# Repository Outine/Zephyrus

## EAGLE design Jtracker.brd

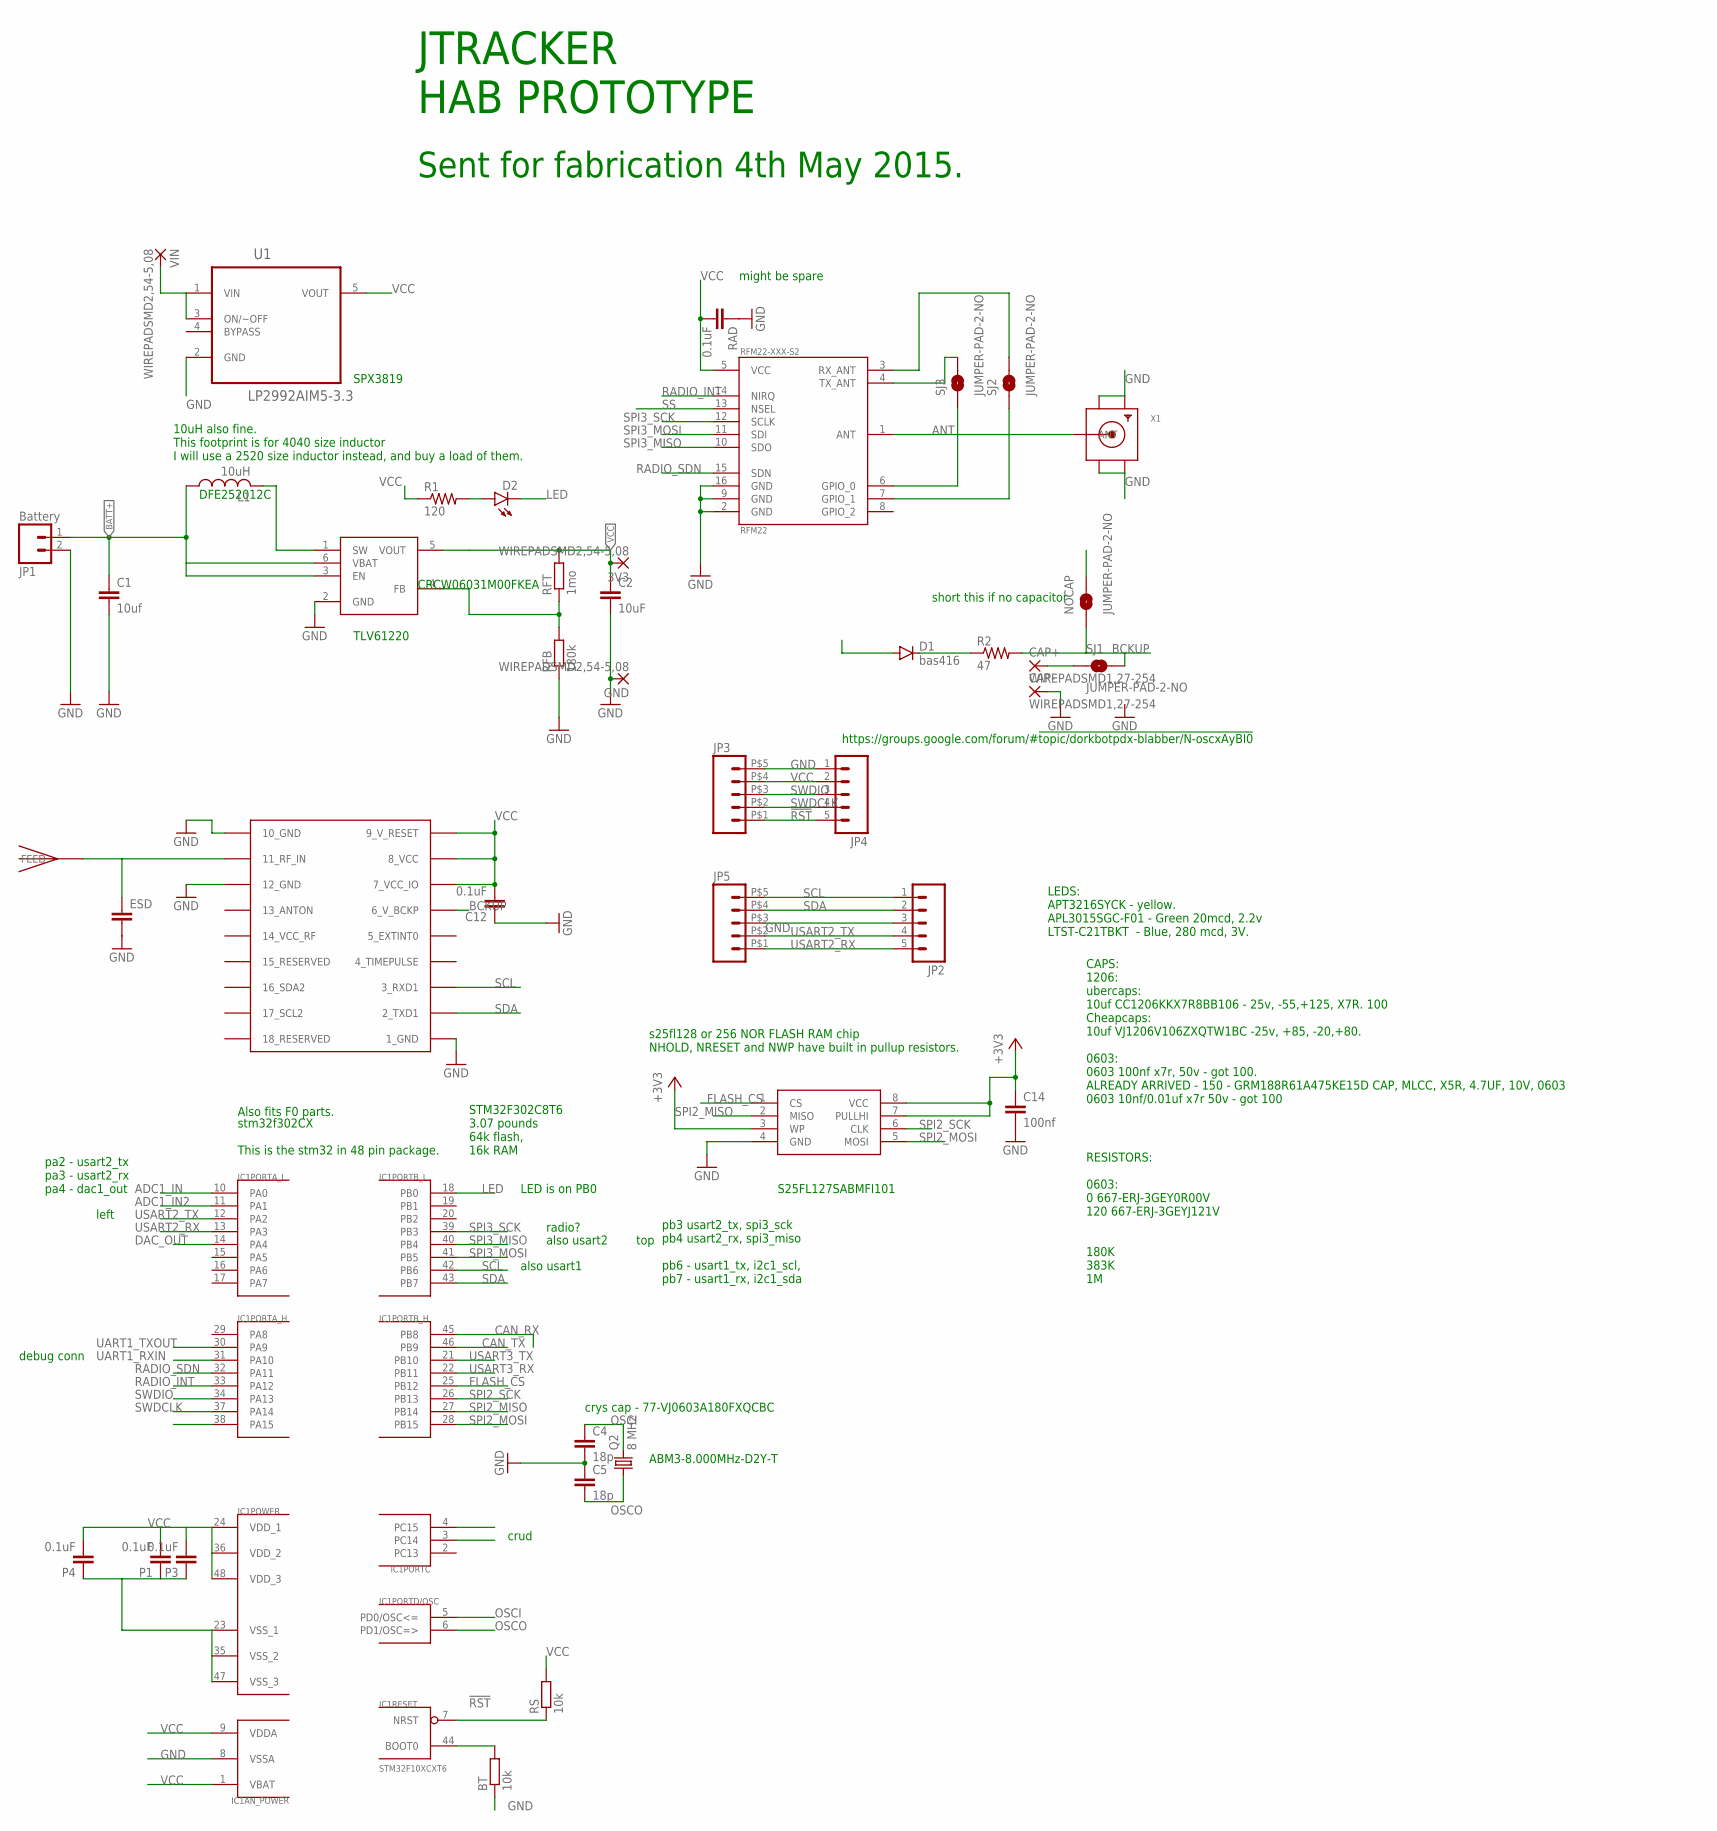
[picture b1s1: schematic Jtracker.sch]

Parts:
3V3: WIREPADSMD2,54-5,08; SMD2,54-5,08
BT: 10k; R0603
C1: 10uf; 1206
C2: 10uF; 1206
C4, C5: 18p; C0603
C12: 0.1uF; C0603
C14: 100nf; 0603-CAP
CAP+: WIREPADSMD1,27-254; SMD1,27-2,54
CAP-: WIREPADSMD1,27-254; SMD1,27-2,54
D1: bas416; SOD-123
D2: LED1206; LED-1206
ESD: CAP0603-CAP; 0603-CAP
GND: WIREPADSMD2,54-5,08; SMD2,54-5,08
GPS_ANT: JTI_ANTENNA-1575AT43A40
IC1: STM32F10XCXT6; TQFP48
JP1: Battery; 1X02
JP2, JP4: M05NO_SILK; 1X05_NO_SILK
JP3, JP5: M05; 5PADSMD
L1: 10uH; LQH44
MEM: S25FL127S_SOIC; SOIC-8W
NOCAP: JUMPER-PAD-2-NO; PAD-JUMPER-2-NO_NO_SILK
P1, P3, P4: 0.1uF; C0603
Q2: 8 MHz; ABRACON_ABM3_CRYSTAL
R1: 120; 0603-RES
R2: 47; 0603-RES
RAD: 0.1uF; C0603
RFB: 180k; R0603
RFM22-XXX-S2: RFM22; RFM22-XXX-S2
RFT: 1mo; R0603
RS: 10k; R0603
SJ1, SJ2, SJ3: JUMPER-PAD-2-NO; PAD-JUMPER-2-NO_NO_SILK
U1: LP2992AIM5-3.3; SOT95P284X122-5N
U$2: TLV61220; SOT23-6
U$3: UBLOX_MAX
VIN: WIREPADSMD2,54-5,08; SMD2,54-5,08
X1: SMACONNECTOR_EDGE_UFL; SMA_EDGELAUNCH_UFL

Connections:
!RST: IC1.7 (NRST), JP3.P$1 (1), JP4.5, RS.1
+3V3: MEM.3 (WP)
ADC1_IN: IC1.10 (PA0)
ADC1_IN2: IC1.11 (PA1)
ANT: RFM22-XXX-S2.1 (ANT), X1.P (ANT)
BATT+: C1.1, JP1.1, L1.P$1 (1), U$2.3 (EN), U$2.6 (VBAT)
BCKUP: NOCAP.1, R2.2, SJ1.2, U$3.6_V_BCKP
CAN_RX: IC1.45 (PB8)
CAN_TX: IC1.46 (PB9)
DAC_OUT: IC1.14 (PA4)
FLASH_CS: IC1.25 (PB12), MEM.1 (CS)
GND: BT.1, C1.2, C2.2, C4.2, C5.1, C12.1, C14.2, CAP-.1, ESD.2, GND.1, IC1.8 (VSSA), IC1.23 (VSS_1), IC1.35 (VSS_2), IC1.47 (VSS_3), JP1.2, JP2.3, JP3.P$5 (5), JP4.1, JP5.P$3 (3), MEM.4 (GND), P1.1, P3.1, P4.1, RAD.1, RFB.1, RFM22-XXX-S2.2 (GND), RFM22-XXX-S2.9 (GND), RFM22-XXX-S2.16 (GND), U1.2 (GND), U$2.2 (GND), U$3.1_GND, U$3.10_GND, U$3.12_GND, X1.GND@1 (GND1), X1.GND@2 (GND2), X1.GND@3 (GND3), X1.GND@4 (GND4)
GPS_ANT: ESD.1, GPS_ANT.FEED, U$3.11_RF_IN
LED: D2.C, IC1.18 (PB0)
unnamed: D1.C, R2.1
unnamed: U1.1 (VIN), U1.3 (ON/~OFF), VIN.1
unnamed: BT.2, IC1.44 (BOOT0)
unnamed: RFM22-XXX-S2.4 (TX_ANT), SJ3.2
unnamed: RFM22-XXX-S2.3 (RX_ANT), SJ2.2
unnamed: L1.P$2 (2), U$2.1 (SW)
unnamed: CAP+.1, SJ1.1
unnamed: RFM22-XXX-S2.7 (GPIO_1), SJ2.1
unnamed: RFB.2, RFT.1, U$2.4 (FB)
unnamed: RFM22-XXX-S2.6 (GPIO_0), SJ3.1
unnamed: D2.A, R1.2
OSCI: C4.1, IC1.5 (PD0/OSC<=), Q2.P$2 (2)
OSCO: C5.2, IC1.6 (PD1/OSC=>), Q2.P$1 (1)
RADIO_INT: IC1.33 (PA12), RFM22-XXX-S2.14 (NIRQ)
RADIO_SDN: IC1.32 (PA11), RFM22-XXX-S2.15 (SDN)
SCL: IC1.42 (PB6), JP2.1, JP5.P$5 (5), U$3.3_RXD1
SDA: IC1.43 (PB7), JP2.2, JP5.P$4 (4), U$3.2_TXD1
SPI2_MISO: IC1.27 (PB14), MEM.2 (MISO)
SPI2_MOSI: IC1.28 (PB15), MEM.5 (MOSI)
SPI2_SCK: IC1.26 (PB13), MEM.6 (CLK)
SPI3_MISO: IC1.40 (PB4), RFM22-XXX-S2.10 (SDO)
SPI3_MOSI: IC1.41 (PB5), RFM22-XXX-S2.11 (SDI)
SPI3_SCK: IC1.39 (PB3), RFM22-XXX-S2.12 (SCLK)
SS: IC1.38 (PA15), RFM22-XXX-S2.13 (NSEL)
SWDCLK: IC1.37 (PA14), JP3.P$2 (2), JP4.4
SWDIO: IC1.34 (PA13), JP3.P$3 (3), JP4.3
UART1_RXIN: IC1.31 (PA10)
UART1_TXOUT: IC1.30 (PA9)
USART2_RX: IC1.13 (PA3), JP2.5, JP5.P$1 (1)
USART2_TX: IC1.12 (PA2), JP2.4, JP5.P$2 (2)
USART3_RX: IC1.22 (PB11)
USART3_TX: IC1.21 (PB10)
VCC: 3V3.1, C2.1, C12.2, C14.1, D1.A, IC1.1 (VBAT), IC1.9 (VDDA), IC1.24 (VDD_1), IC1.36 (VDD_2), IC1.48 (VDD_3), JP3.P$4 (4), JP4.2, MEM.7 (PULLHI), MEM.8 (VCC), NOCAP.2, P1.2, P3.2, P4.2, R1.1, RAD.2, RFM22-XXX-S2.5 (VCC), RFT.2, RS.2, U1.5 (VOUT), U$2.5 (VOUT), U$3.7_VCC_IO, U$3.8_VCC, U$3.9_V_RESET

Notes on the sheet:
https://groups.google.com/forum/#!topic/dorkbotpdx-blabber/N-oscxAyBI0
stm32f302CX This is the stm32 in 48 pin package.
also usart1
also usart2
radio?
debug conn
crud
left
top
pb3 usart2_tx, spi3_sck pb4 usart2_rx, spi3_miso pb6 - usart1_tx, i2c1_scl, pb7 - usart1_rx, i2c1_sda
pa2 - usart2_tx pa3 - usart2_rx pa4 - dac1_out
s25fl128 or 256 NOR FLASH RAM chip NHOLD, NRESET and NWP have built in pullup resistors.
short this if no capacitor
might be spare
10uH also fine. This footprint is for 4040 size inductor I will use a 2520 size inductor instead, and buy a load of them.
JTRACKER HAB PROTOTYPE
Sent for fabrication 4th May 2015.
ABM3-8.000MHz-D2Y-T
TLV61220
crys cap - 77-VJ0603A180FXQCBC
S25FL127SABMFI101
CRCW06031M00FKEA
DFE252012C
SPX3819
STM32F302C8T6 3.07 pounds 64k flash, 16k RAM
LEDS: APT3216SYCK - yellow. APL3015SGC-F01 - Green 20mcd, 2.2v LTST-C21TBKT - Blue, 280 mcd, 3V.
CAPS: 1206: ubercaps: 10uf CC1206KKX7R8BB106 - 25v, -55,+125, X7R. 100 Cheapcaps: 10uf VJ1206V106ZXQTW1BC -25v, +85, -20,+80. 0603: 0603 100nf x7r, 50v - got 100. ALREADY ARRIVED - 150 - GRM188R61A475KE15D CAP, MLCC, X5R, 4.7UF, 10V, 0603 0603 10nf/0.01uf x7r 50v - got 100
RESISTORS: 0603: 0 667-ERJ-3GEY0R00V 120 667-ERJ-3GEYJ121V 180K 383K 1M
Also fits F0 parts.
LED is on PB0

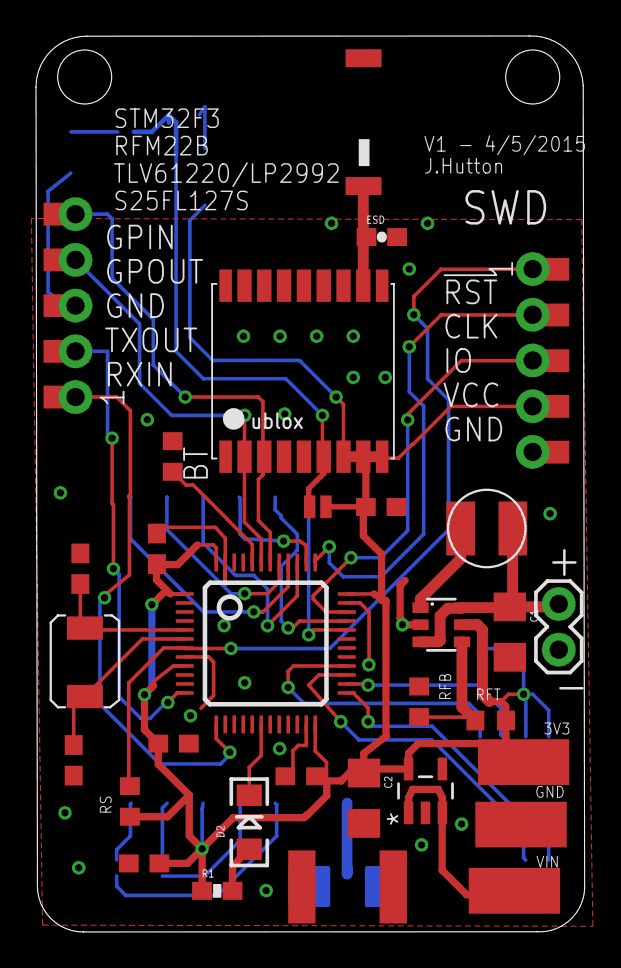
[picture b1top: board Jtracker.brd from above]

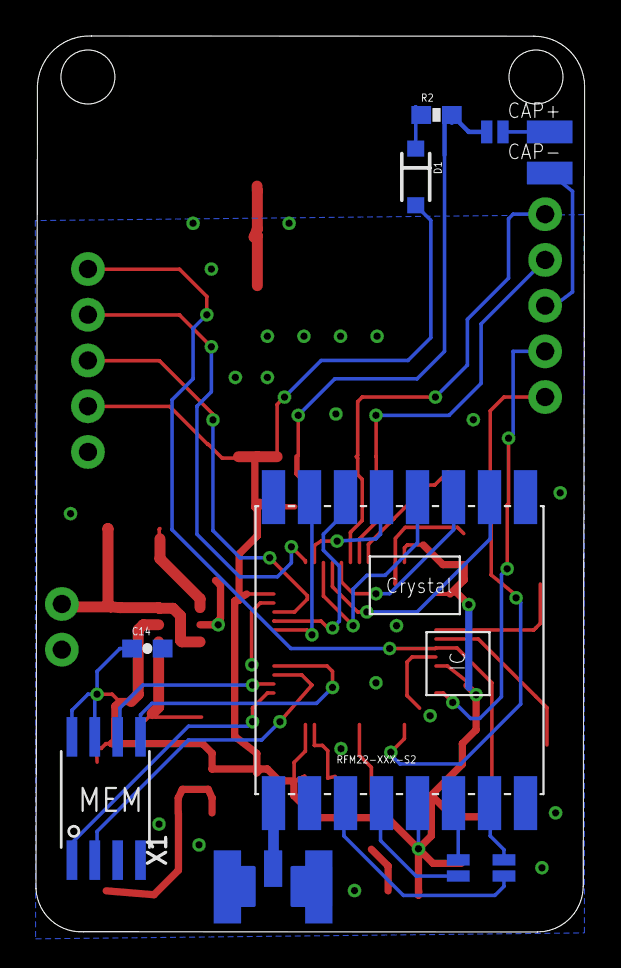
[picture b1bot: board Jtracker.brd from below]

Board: 2 copper layers, 30.5 x 49.8 mm, 43 parts (11 on the bottom side), 37 nets.

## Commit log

2015-11-08 Tidying up project for git commit

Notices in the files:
parts and their libraries:
SparkFun-DiscreteSemi: Licensing: Creative Commons ShareAlike 4.0 International - https://creativecommons.org/licenses/by-sa/4.0
